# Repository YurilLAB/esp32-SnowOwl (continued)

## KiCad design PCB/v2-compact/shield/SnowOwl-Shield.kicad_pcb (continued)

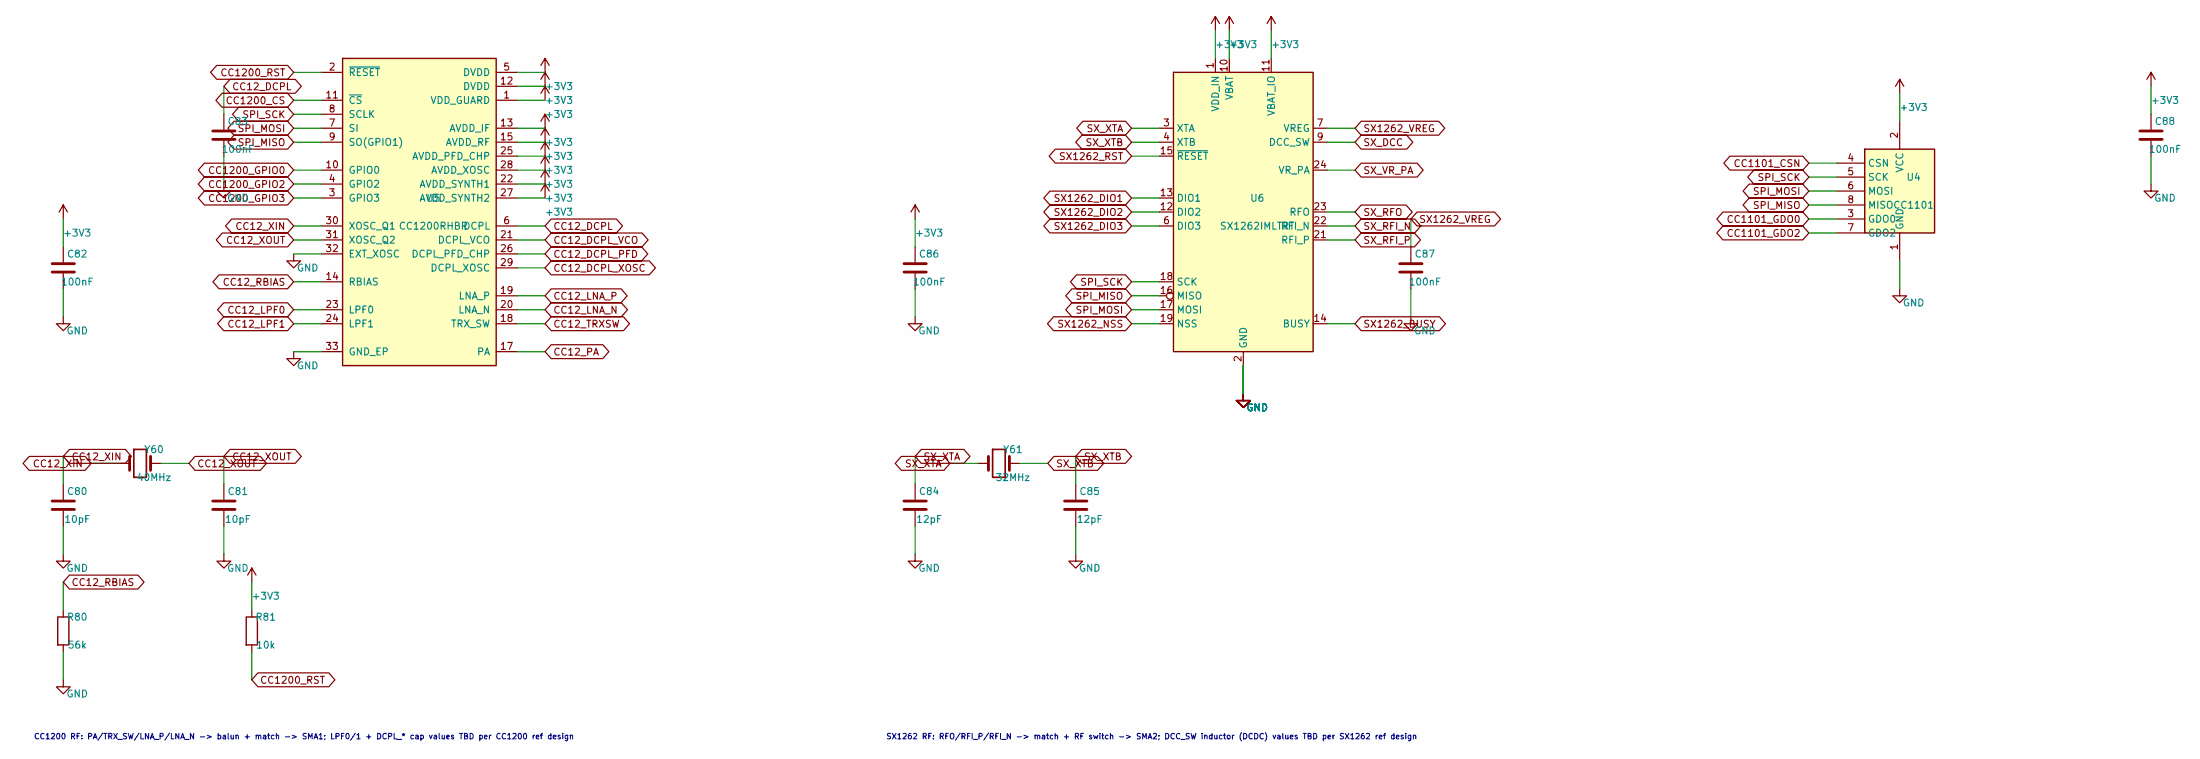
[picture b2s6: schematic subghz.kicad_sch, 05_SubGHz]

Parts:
C80, C81: 10pF; C_0402_1005Metric
C82, C83, C86, C87, C88: 100nF; C_0402_1005Metric
C84, C85: 12pF; C_0402_1005Metric
R80: 56k; R_0402_1005Metric
R81: 10k; R_0402_1005Metric
U4: CC1101; PinHeader_2x04_P2.54mm_Vertical
U5: CC1200RHBR; QFN-32-1EP_5x5mm_P0.5mm_EP3.45x3.45mm
U6: SX1262IMLTRT; QFN-24-1EP_4x4mm_P0.5mm_EP2.6x2.6mm
Y60: 40MHz; Crystal_SMD_3225-4Pin_3.2x2.5mm
Y61: 32MHz; Crystal_SMD_3225-4Pin_3.2x2.5mm

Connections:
+3V3: C82.1, C86.1, C88.1, R81.1, U4.2 (VCC), U5.1 (VDD_GUARD), U5.5 (DVDD), U5.12 (DVDD), U5.13 (AVDD_IF), U5.15 (AVDD_RF), U5.22 (AVDD_SYNTH1), U5.25 (AVDD_PFD_CHP), U5.27 (AVDD_SYNTH2), U5.28 (AVDD_XOSC), U6.1 (VDD_IN), U6.10 (VBAT), U6.11 (VBAT_IO); also elsewhere on the board
CC12_DCPL: C83.1, U5.6 (DCPL)
CC12_DCPL_PFD: U5.26 (DCPL_PFD_CHP)
CC12_DCPL_VCO: U5.21 (DCPL_VCO)
CC12_DCPL_XOSC: U5.29 (DCPL_XOSC)
CC12_LNA_N: U5.20 (LNA_N)
CC12_LNA_P: U5.19 (LNA_P)
CC12_LPF0: U5.23 (LPF0)
CC12_LPF1: U5.24 (LPF1)
CC12_PA: U5.17 (PA)
CC12_RBIAS: R80.1, U5.14 (RBIAS)
CC12_TRXSW: U5.18 (TRX_SW)
CC12_XIN: C80.1, U5.30 (XOSC_Q1), Y60.1
CC12_XOUT: C81.1, U5.31 (XOSC_Q2), Y60.2
CC1101_CSN: U4.4 (CSN); also elsewhere on the board
CC1101_GDO0: U4.3 (GDO0); also elsewhere on the board
CC1101_GDO2: U4.7 (GDO2)
CC1200_CS: U5.11 (~CS); also elsewhere on the board
CC1200_GPIO0: U5.10 (GPIO0); also elsewhere on the board
CC1200_GPIO2: U5.4 (GPIO2)
CC1200_GPIO3: U5.3 (GPIO3)
CC1200_RST: R81.2, U5.2 (~RESET)
SPI_MISO: U4.8 (MISO), U5.9 (SO(GPIO1)), U6.16 (MISO); also elsewhere on the board
SPI_MOSI: U4.6 (MOSI), U5.7 (SI), U6.17 (MOSI); also elsewhere on the board
SPI_SCK: U4.5 (SCK), U5.8 (SCLK), U6.18 (SCK); also elsewhere on the board
SX1262_BUSY: U6.14 (BUSY); also elsewhere on the board
SX1262_DIO1: U6.13 (DIO1); also elsewhere on the board
SX1262_DIO2: U6.12 (DIO2)
SX1262_DIO3: U6.6 (DIO3)
SX1262_NSS: U6.19 (NSS); also elsewhere on the board
SX1262_RST: U6.15 (~RESET); also elsewhere on the board
SX1262_VREG: C87.1, U6.7 (VREG)
SX_DCC: U6.9 (DCC_SW)
SX_RFI_N: U6.22 (RFI_N)
SX_RFI_P: U6.21 (RFI_P)
SX_RFO: U6.23 (RFO)
SX_VR_PA: U6.24 (VR_PA)
SX_XTA: C84.1, U6.3 (XTA), Y61.1
SX_XTB: C85.1, U6.4 (XTB), Y61.2

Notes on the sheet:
CC1200 RF: PA/TRX_SW/LNA_P/LNA_N -> balun + match -> SMA1; LPF0/1 + DCPL_* cap values TBD per CC1200 ref design
SX1262 RF: RFO/RFI_P/RFI_N -> match + RF switch -> SMA2; DCC_SW inductor (DCDC) values TBD per SX1262 ref design

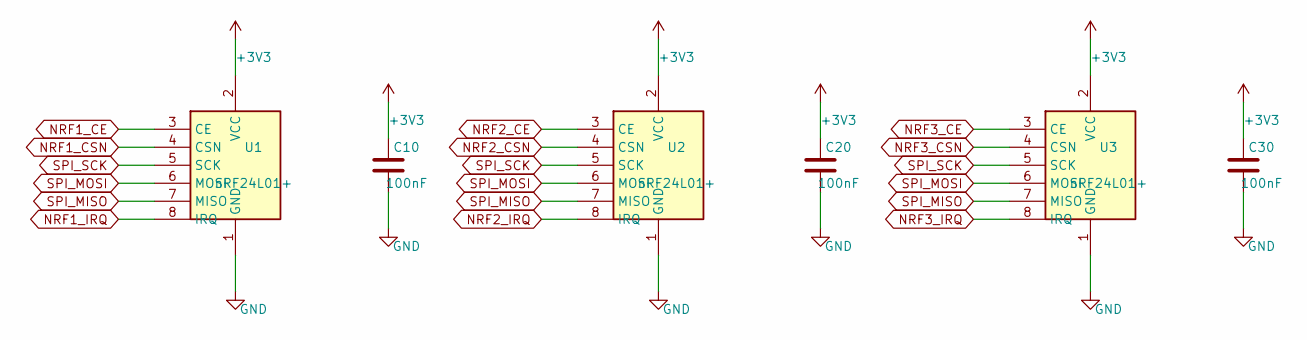
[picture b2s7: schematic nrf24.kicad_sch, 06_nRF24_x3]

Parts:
C10, C20, C30: 100nF; C_0402_1005Metric
U1, U2, U3: nRF24L01+; PinHeader_2x04_P2.54mm_Vertical

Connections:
+3V3: C10.1, C20.1, C30.1, U1.2 (VCC), U2.2 (VCC), U3.2 (VCC); also elsewhere on the board
NRF1_CE: U1.3 (CE); also elsewhere on the board
NRF1_CSN: U1.4 (CSN); also elsewhere on the board
NRF1_IRQ: U1.8 (IRQ); also elsewhere on the board
NRF2_CE: U2.3 (CE); also elsewhere on the board
NRF2_CSN: U2.4 (CSN); also elsewhere on the board
NRF2_IRQ: U2.8 (IRQ); also elsewhere on the board
NRF3_CE: U3.3 (CE); also elsewhere on the board
NRF3_CSN: U3.4 (CSN); also elsewhere on the board
NRF3_IRQ: U3.8 (IRQ); also elsewhere on the board
SPI_MISO: U1.7 (MISO), U2.7 (MISO), U3.7 (MISO); also elsewhere on the board
SPI_MOSI: U1.6 (MOSI), U2.6 (MOSI), U3.6 (MOSI); also elsewhere on the board
SPI_SCK: U1.5 (SCK), U2.5 (SCK), U3.5 (SCK); also elsewhere on the board

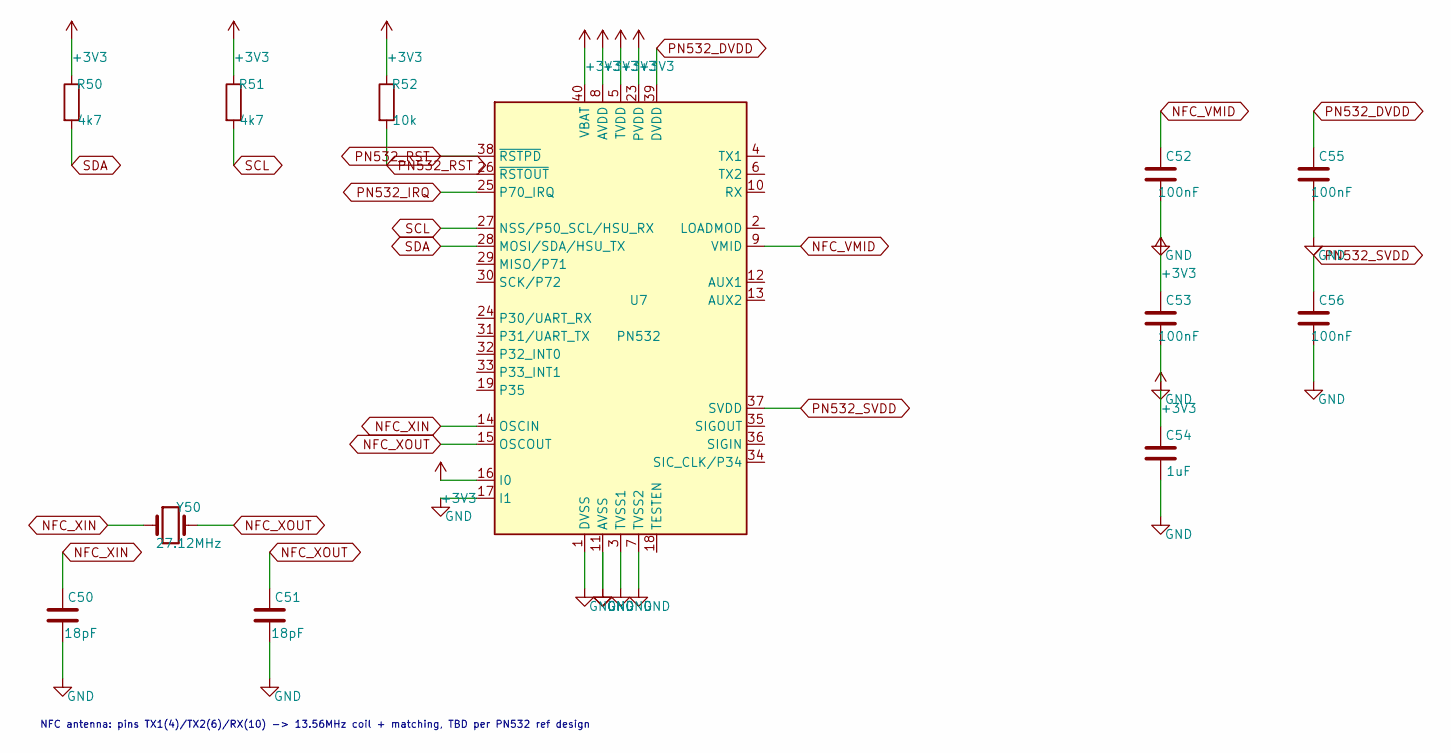
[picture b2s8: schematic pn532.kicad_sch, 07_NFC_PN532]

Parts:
C50, C51: 18pF; C_0402_1005Metric
C52, C53, C55, C56: 100nF; C_0402_1005Metric
C54: 1uF; C_0402_1005Metric
R50, R51: 4k7; R_0402_1005Metric
R52: 10k; R_0402_1005Metric
U7: PN532; HVQFN-40-1EP_6x6mm_P0.5mm_EP4.1x4.1mm
Y50: 27.12MHz; Crystal_SMD_3225-4Pin_3.2x2.5mm

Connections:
+3V3: C53.1, C54.1, R50.1, R51.1, R52.1, U7.5 (TVDD), U7.8 (AVDD), U7.16 (I0), U7.23 (PVDD), U7.40 (VBAT); also elsewhere on the board
NFC_VMID: C52.1, U7.9 (VMID)
NFC_XIN: C50.1, U7.14 (OSCIN), Y50.1
NFC_XOUT: C51.1, U7.15 (OSCOUT), Y50.2
PN532_DVDD: C55.1, U7.39 (DVDD)
PN532_IRQ: U7.25 (P70_IRQ)
PN532_RST: R52.2, U7.38 (~RSTPD)
PN532_SVDD: C56.1, U7.37 (SVDD)
SCL: R51.2, U7.27 (NSS/P50_SCL/HSU_RX); also elsewhere on the board
SDA: R50.2, U7.28 (MOSI/SDA/HSU_TX); also elsewhere on the board

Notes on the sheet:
NFC antenna: pins TX1(4)/TX2(6)/RX(10) -> 13.56MHz coil + matching, TBD per PN532 ref design

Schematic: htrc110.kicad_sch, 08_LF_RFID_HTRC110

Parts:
C90, C91: 18pF; C_0402_1005Metric
C92: 100nF; C_0402_1005Metric
C93: 10uF; C_0402_1005Metric
R90: 10k; R_0402_1005Metric
U8: HTRC11001T; SOIC-14_3.9x8.7mm_P1.27mm
Y90: 4MHz; Crystal_SMD_3225-4Pin_3.2x2.5mm

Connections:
+3V3: R90.1; also elsewhere on the board
HTRC_DIN: U8.8 (DIN); also elsewhere on the board
HTRC_DOUT: R90.2, U8.10 (DOUT); also elsewhere on the board
HTRC_MODE: U8.5 (MODE); also elsewhere on the board
HTRC_SCLK: U8.9 (SCLK); also elsewhere on the board
HTRC_XIN: C90.1, U8.6 (XTAL1), Y90.1
HTRC_XOUT: C91.1, U8.7 (XTAL2), Y90.2
LF_RX: U8.11 (RX)
LF_TX1: U8.4 (TX1)
LF_TX2: U8.2 (TX2)

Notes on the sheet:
HTRC110 is 5V; DOUT open-drain pulled to 3.3V. 3-wire SCLK/DIN from the C5 (3.3V) may need level care. 125kHz LF coil tank on LF_TX1/TX2/RX TBD. VERIFY pins 8-14 vs datasheet.

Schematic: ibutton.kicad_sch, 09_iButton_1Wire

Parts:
J91: iButton; PinHeader_1x02_P2.54mm_Vertical
R93: 4k7; R_0402_1005Metric

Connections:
+3V3: R93.1; also elsewhere on the board
OW_1WIRE: J91.1, R93.2; also elsewhere on the board

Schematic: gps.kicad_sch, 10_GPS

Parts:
C70: 100nF; C_0402_1005Metric
C71: 10uF; C_0402_1005Metric
C72: 1uF; C_0402_1005Metric
R55: 0R; R_0402_1005Metric
R58: 10k; R_0402_1005Metric
U9: NEO-M9N; ublox_NEO

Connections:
+3V3: C70.1, C71.1, C72.1, R55.1, R58.1, U9.1 (~SAFEBOOT), U9.2 (D_SEL), U9.7 (VDD_USB), U9.22 (V_BCKP), U9.23 (VCC); also elsewhere on the board
GPS_ANT: U9.11 (RF_IN)
GPS_LNA_EN: U9.14 (LNA_EN)
GPS_RST: R58.2, U9.8 (~RESET)
GPS_RX: U9.21 (RXD/SPI_MOSI); also elsewhere on the board
GPS_TX: U9.20 (TXD/SPI_MISO); also elsewhere on the board
GPS_VCC_RF: R55.2, U9.9 (VCC_RF)

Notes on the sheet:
GPS active-antenna bias-tee on GPS_ANT (L+C) TBD; GPS_TX/RX go to the ESP32-C5

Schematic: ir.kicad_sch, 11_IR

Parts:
C58: 100nF; C_0402_1005Metric
D1: IR_LED; LED_0805_2012Metric
Q1: MMBT3904; SOT-23
R56: 33R; R_0402_1005Metric
R57: 220R; R_0402_1005Metric
U11: TSOP38238; Vishay_CAST-3Pin

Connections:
+3V3: C58.1, U11.2 (Vs); also elsewhere on the board
IRLED_A: D1.2 (A), R56.2
IRLED_B: Q1.1 (B), R57.2
IRLED_K: D1.1 (K), Q1.2 (C)
IR_RX: U11.3 (OUT); also elsewhere on the board
IR_TX: R57.1; also elsewhere on the board

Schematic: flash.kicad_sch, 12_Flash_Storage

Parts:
C12: 100nF; C_0402_1005Metric
U12: W25Q128JVSSIQ; SOIC-8_3.9x4.9mm_P1.27mm

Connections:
+3V3: C12.1, U12.3 (~WP/IO_{2}), U12.7 (~HOLD/~RESET/IO_{3}), U12.8 (VCC); also elsewhere on the board
FLASH_CS: U12.1 (~CS); also elsewhere on the board
SPI_MISO: U12.2 (DO/IO_{1}); also elsewhere on the board
SPI_MOSI: U12.5 (DI/IO_{0}); also elsewhere on the board
SPI_SCK: U12.6 (CLK); also elsewhere on the board

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
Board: 4 copper layers, 102 parts (47 on the bottom side), 91 nets, no tracks yet.

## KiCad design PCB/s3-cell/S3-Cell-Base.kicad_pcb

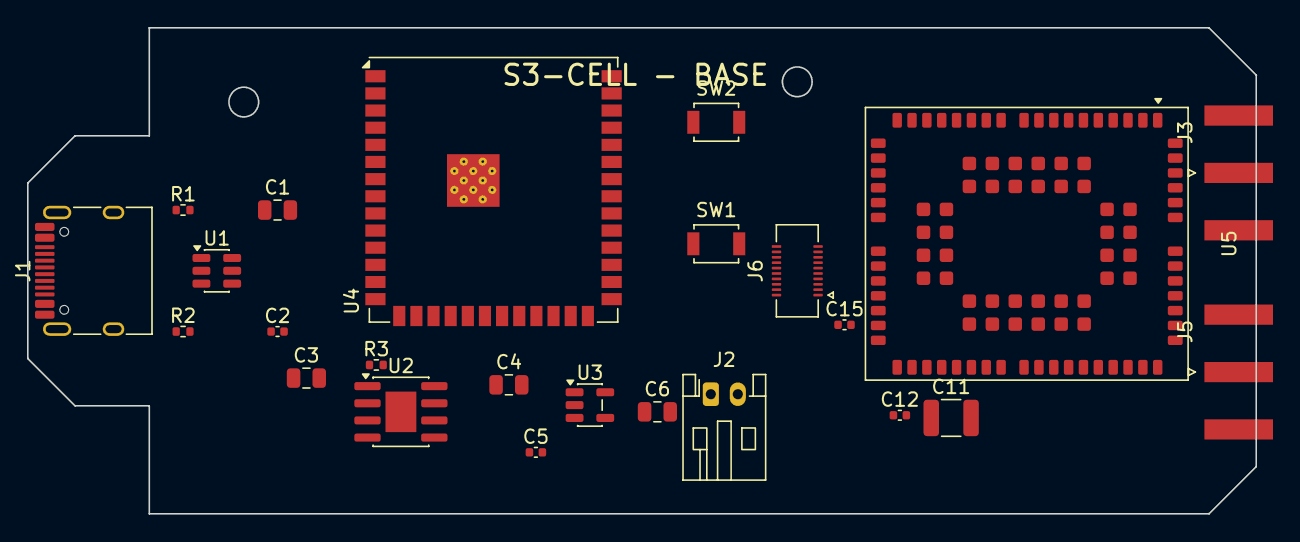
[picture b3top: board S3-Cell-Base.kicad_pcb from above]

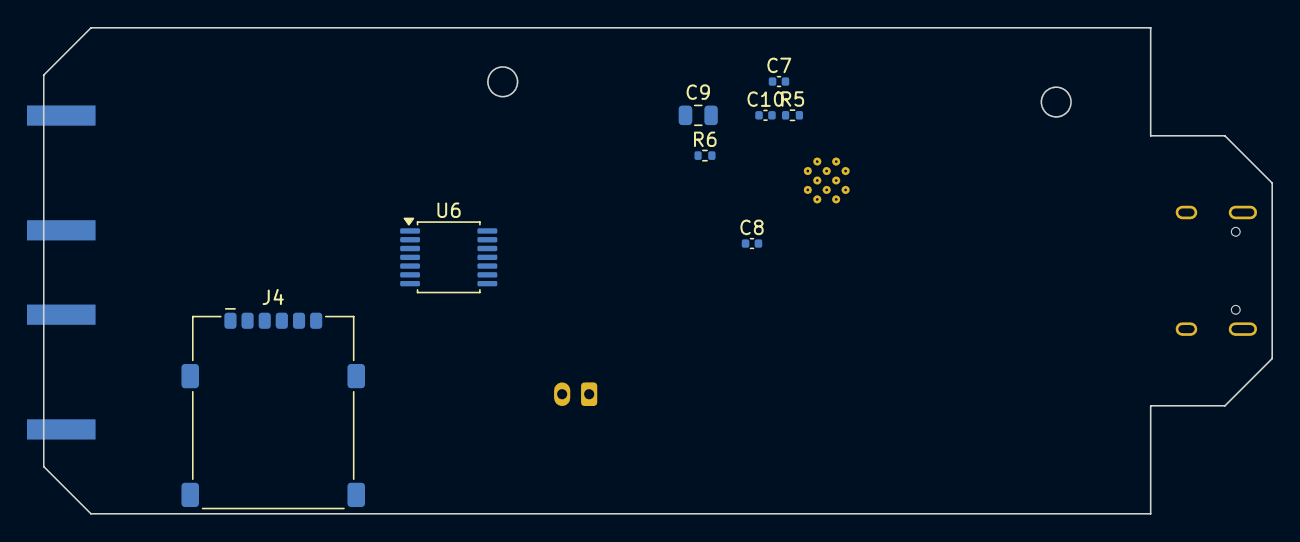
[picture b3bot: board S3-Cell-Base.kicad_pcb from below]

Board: 4 copper layers, 91.0 x 36.0 mm, 32 parts (8 on the bottom side), 14 nets, no tracks yet.

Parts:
C1, C3, C4, C6: 10uF; C_0805_2012Metric
C2, C7, C8, C12, C15: 100nF; C_0402_1005Metric
C5, C10: 1uF; C_0402_1005Metric
C9: 22uF; C_0805_2012Metric
C11: 100uF; C_1210_3225Metric
J1: USB-C; USB_C_Receptacle_HRO_TYPE-C-31-M-12
J2: BATT; JST_PH_S2B-PH-K_1x02_P2.00mm_Horizontal
J3: SMA; SMA_Amphenol_132289_EdgeMount
J4: nanoSIM; nanoSIM_GCT_SIM8060-6-0-14-00
J5: SMA_GNSS; SMA_Amphenol_132289_EdgeMount
J6: DF40C-2x10 (stack); Hirose_DF40C(2.0)-20DS-0.4V_2x10_P0.4mm
R1, R2: 5.1k; R_0402_1005Metric
R3: 1.2k; R_0402_1005Metric
R5, R6: 10k; R_0402_1005Metric
SW1: BOOT; SW_SPST_B3U-1000P
SW2: RST; SW_SPST_B3U-1000P
U1: USBLC6-2SC6; SOT-23-6
U2: TP4056; SOIC-8-1EP_3.9x4.9mm_P1.27mm_EP2.29x3mm
U3: AP2112-3.3; SOT-23-5
U4: ESP32-S3-WROOM-1U
U5: BG95-M3; Quectel_BG95
U6: TXB0104; TSSOP-14_4.4x5mm_P0.65mm

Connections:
+3V3: C6.1, C7.1, C8.1, C9.1, R5.2, R6.2, U3.5, U4.2
ANT_GNSS: J5.1, U5.49
ANT_MAIN: J3.1, U5.60
EN: C10.1, R5.1, SW2.1, U4.3
GND: C1.2, C2.2, C3.2, C4.2, C5.2, C6.2, C7.2, C8.2, C9.2, C10.2, C11.2, C12.2, C15.2, J1.A1, J1.A8, J1.A12, J1.B1, J1.B8, J1.B12, J1.SH, J2.2, J3.2, J4.SH, J5.2, R1.2, R2.2, R3.2, SW1.2, SW2.2, U1.2, U2.1, U2.3, U2.9, U3.2, U4.1, U4.40, U4.41, U5.47
IO0: R6.1, SW1.1, U4.27
PROG: R3.1, U2.2
USB_CC1: J1.A5, R1.1
USB_CC2: J1.B5, R2.1
USB_DM: J1.A7, J1.B7, U1.3, U1.4, U4.13
USB_DP: J1.A6, J1.B6, U1.1, U1.6, U4.14
VBAT: C4.1, C5.1, C11.1, C12.1, J2.1, U2.5, U2.6, U3.1, U3.3, U5.32, U5.33, U5.52, U5.53
VBUS: C1.1, C2.1, C3.1, J1.A4, J1.A9, J1.B4, J1.B9, U1.5, U2.4
VDD_EXT: C15.1, U5.29

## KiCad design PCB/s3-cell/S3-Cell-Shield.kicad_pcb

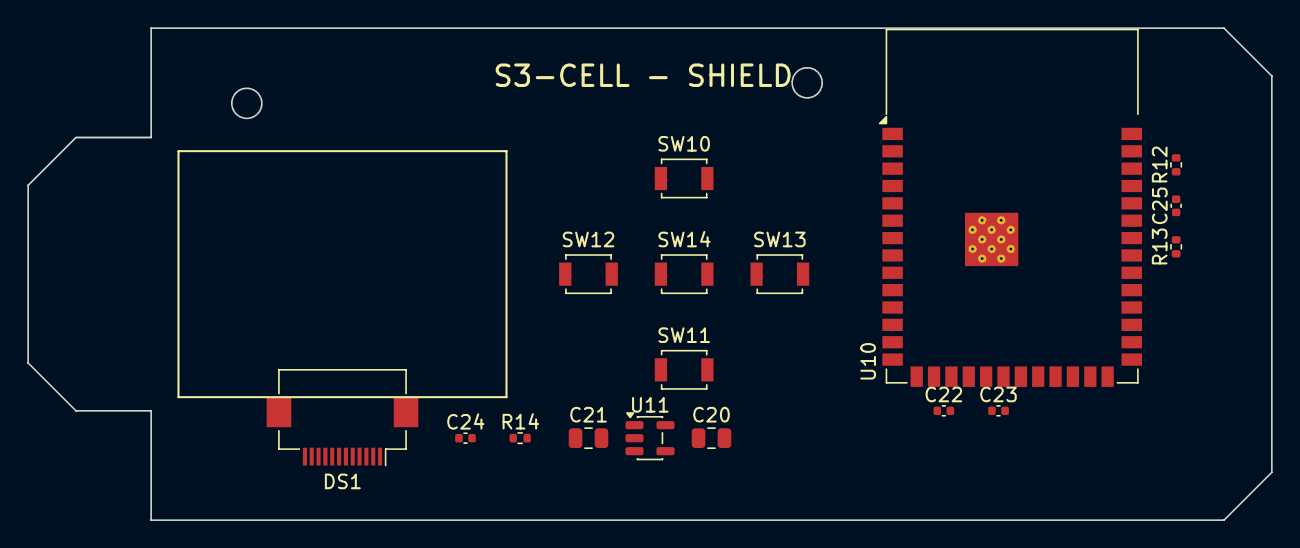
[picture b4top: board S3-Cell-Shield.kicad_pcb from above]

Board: 4 copper layers, 91.0 x 36.0 mm, 18 parts (1 on the bottom side), 3 nets, no tracks yet.

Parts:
C20, C21: 10uF; C_0805_2012Metric
C22, C23, C24, C25: 100nF; C_0402_1005Metric
DS1: TFT 1.14" ST7789; Hirose_FH12-12S-0.5SH_1x12-1MP_P0.50mm_Horizontal
J6: DF40C-2x10 (stack); Hirose_DF40C-20DP-0.4V_2x10-1MP_P0.4mm
R12, R13: 10k; R_0402_1005Metric
R14: BL 10R; R_0402_1005Metric
SW10: UP; SW_SPST_B3U-1000P
SW11: DOWN; SW_SPST_B3U-1000P
SW12: LEFT; SW_SPST_B3U-1000P
SW13: RIGHT; SW_SPST_B3U-1000P
SW14: SEL; SW_SPST_B3U-1000P
U10: ESP32-C5-WROOM-1; ESP32-S3-WROOM-1
U11: AP2112-3.3; SOT-23-5

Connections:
+3V3S: C21.1, C22.1, C23.1, R12.1, R13.1, R14.1
C5_EN: C25.1, R12.2
GND: C20.2, C21.2, C22.2, C23.2, C25.2, SW10.2, SW11.2, SW12.2, SW13.2, SW14.2
